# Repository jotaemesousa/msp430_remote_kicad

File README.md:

msp430_remote_kicad
===================

Kicad files for a remote using a msp430 MCU and a nrf24 transceiver from Nordic

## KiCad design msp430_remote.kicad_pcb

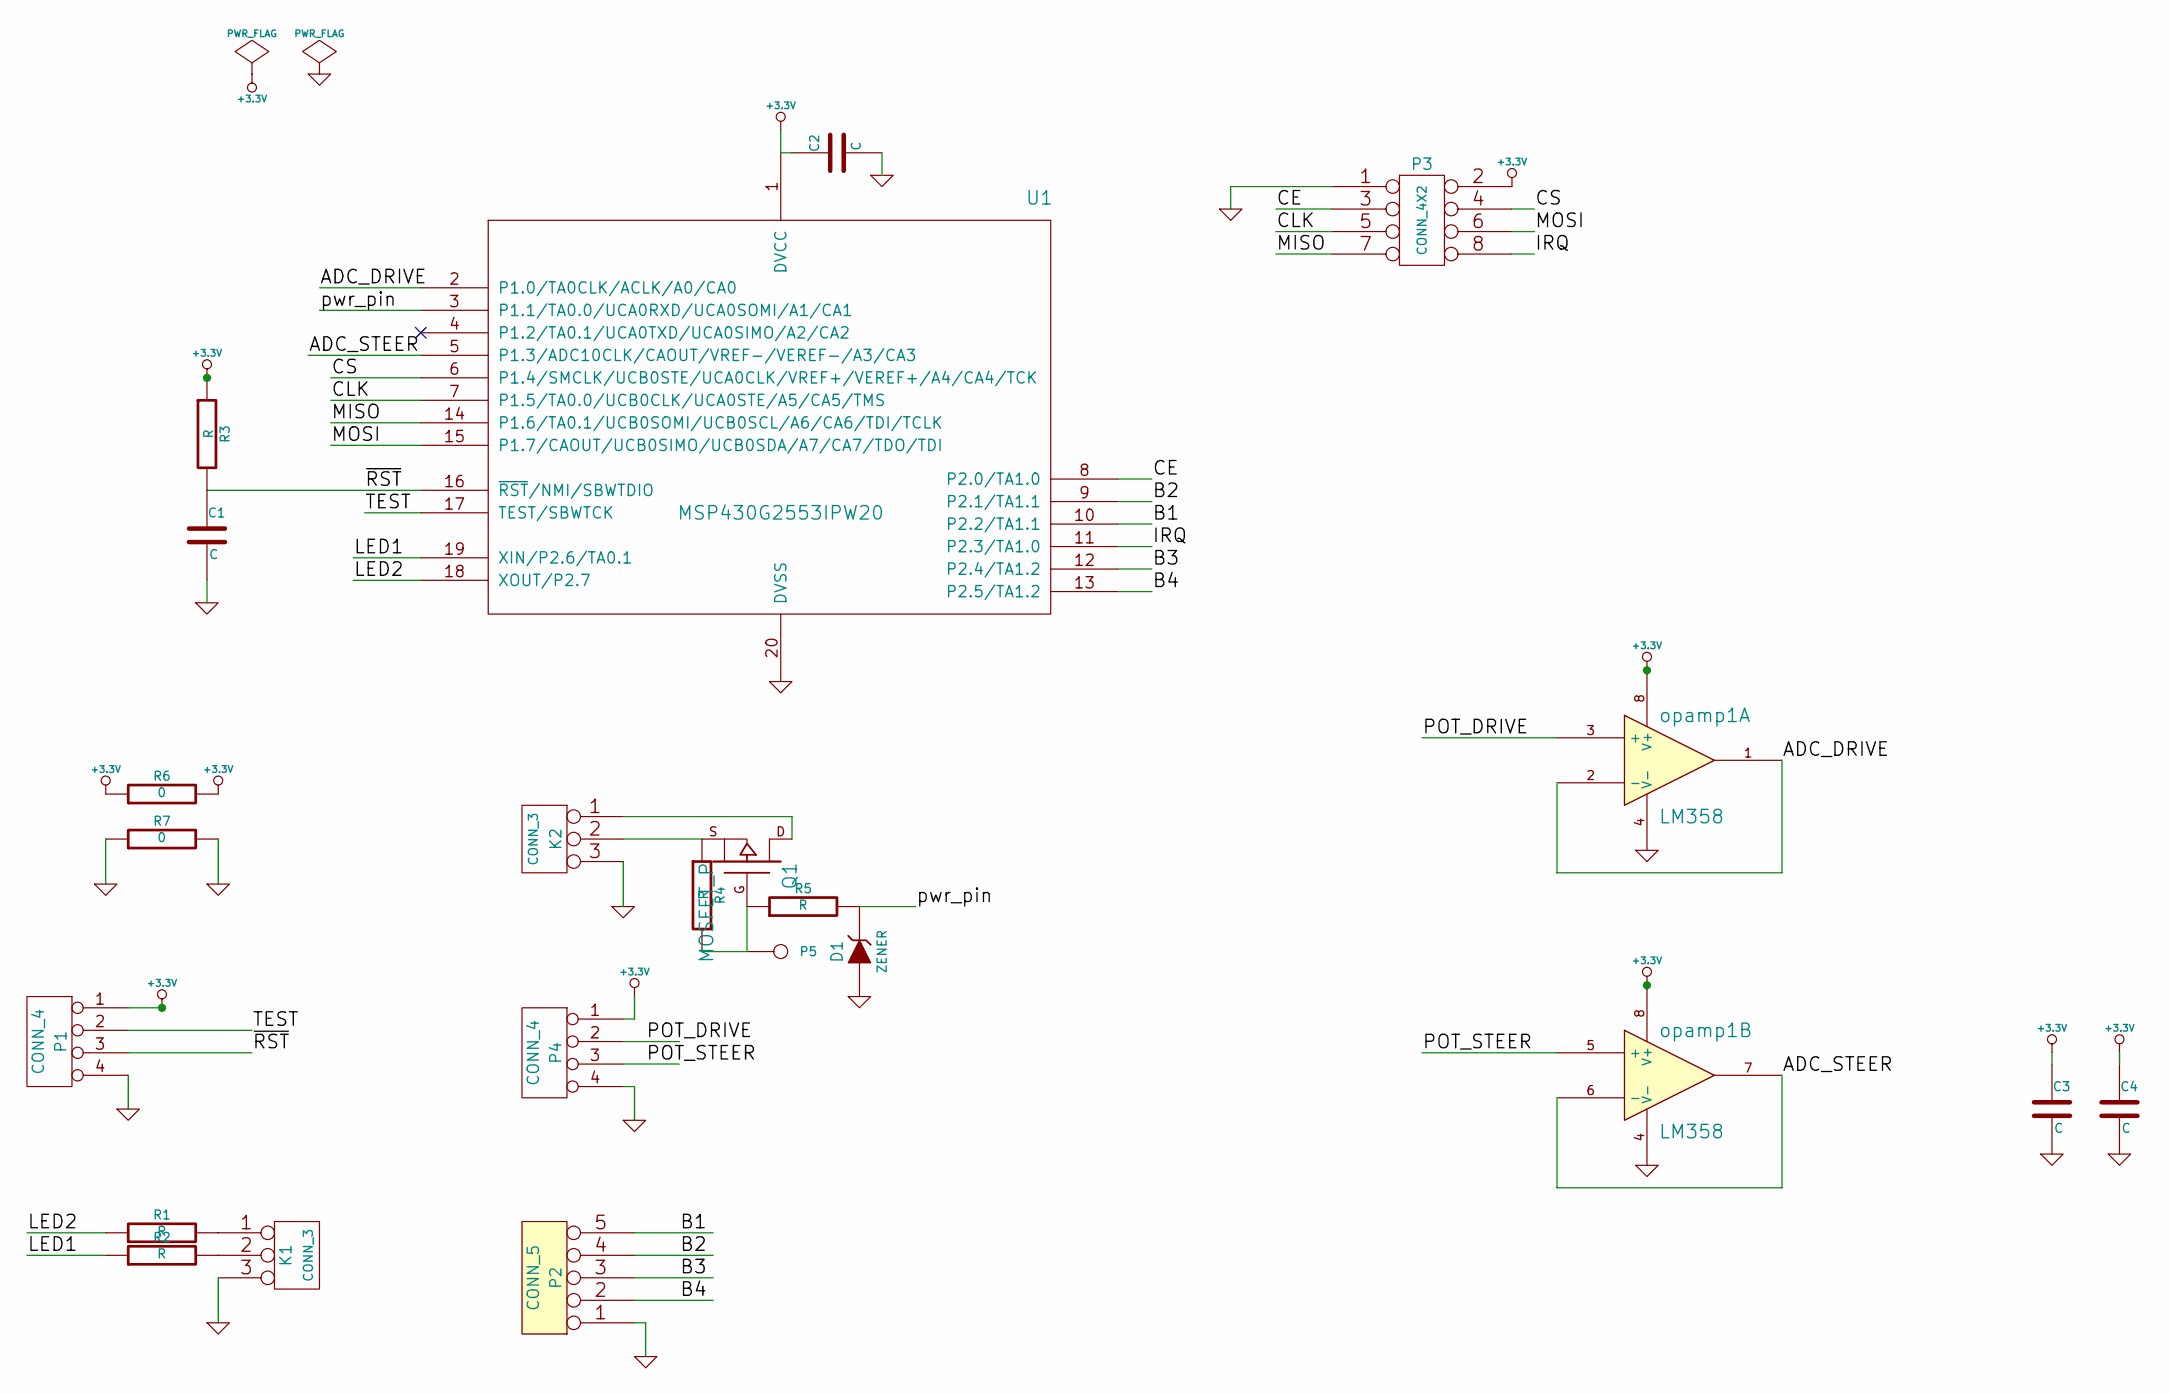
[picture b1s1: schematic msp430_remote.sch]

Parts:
C1, C2, C3, C4: C
D1: ZENER
K1, K2: CONN_3
P1, P4: CONN_4
P2: CONN_5
P3: CONN_4X2
P5: CONN_1
Q1: MOSFET_P
R1, R2, R3, R4, R5: R
R6, R7: 0
U1: MSP430G2553IPW20
opamp1: LM358

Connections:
+3.3V: C2.1, C3.1, C4.1, P1.1, P3.2, P4.1, R3.1, R6.1, R6.2, U1.1 (DVCC), opamp1.8 (V+)
/ADC_DRIVE: U1.2 (P1.0/TA0CLK/ACLK/A0/CA0), opamp1.1, opamp1.2 (-)
/ADC_STEER: U1.5 (P1.3/ADC10CLK/CAOUT/VREF-/VEREF-/A3/CA3), opamp1.6 (-), opamp1.7
/B1: P2.5, U1.10 (P2.2/TA1.1)
/B2: P2.4, U1.9 (P2.1/TA1.1)
/B3: P2.3, U1.12 (P2.4/TA1.2)
/B4: P2.2, U1.13 (P2.5/TA1.2)
/CE: P3.3, U1.8 (P2.0/TA1.0)
/CLK: P3.5, U1.7 (P1.5/TA0.0/UCB0CLK/UCA0STE/A5/CA5/TMS)
/CS: P3.4, U1.6 (P1.4/SMCLK/UCB0STE/UCA0CLK/VREF+/VEREF+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)
/IRQ: P3.8, U1.11 (P2.3/TA1.0)
/LED1: R2.1, U1.19 (XIN/P2.6/TA0.1)
/LED2: R1.1, U1.18 (XOUT/P2.7)
/MISO: P3.7, U1.14 (P1.6/TA0.1/UCB0SOMI/UCB0SCL/A6/CA6/TDI/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)
/MOSI: P3.6, U1.15 (P1.7/CAOUT/UCB0SIMO/UCB0SDA/A7/CA7/TDO/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)
/POT_DRIVE: P4.2, opamp1.3 (+)
/POT_STEER: P4.3, opamp1.5 (+)
/TEST: P1.2, U1.17 (TEST/SBWTCK)
/pwr_pin: D1.2 (K), R5.2, U1.3 (P1.1/TA0.0/UCA0RXD/UCA0SOMI/A1/CA1)
/~RST: C1.1, P1.3, R3.2, U1.16 (~RST~/NMI/SBWTDIO)
GND: C1.2, C2.2, C3.2, C4.2, D1.1 (A), K1.3, K2.3, P1.4, P2.1, P3.1, P4.4, R7.1, R7.2, U1.20 (DVSS), opamp1.4 (V-)
unnamed: K1.1, R1.2
unnamed: K1.2 (PM), R2.2
unnamed: K2.1, Q1.D
unnamed: K2.2 (PM), Q1.S, R4.1
unnamed: P5.1, Q1.G, R4.2, R5.1

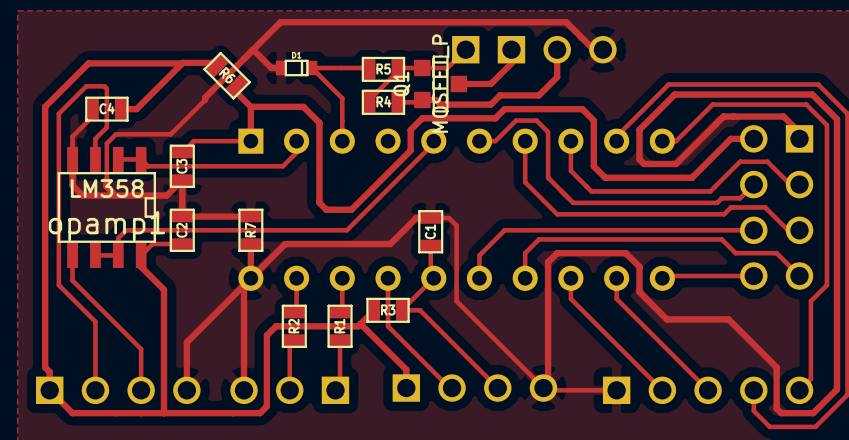
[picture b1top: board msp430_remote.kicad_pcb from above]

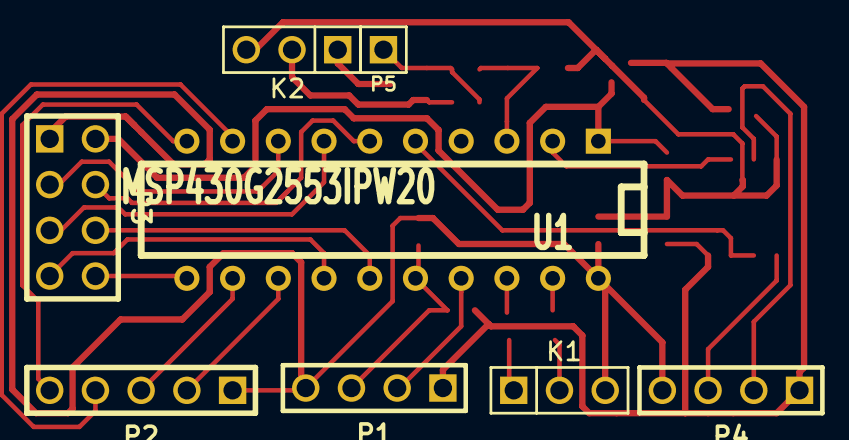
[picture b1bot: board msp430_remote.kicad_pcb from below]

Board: 2 copper layers, 22 parts (8 on the bottom side), 26 nets.

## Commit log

2013-05-23 falta o dc dc
2013-05-25 tudo_feito
2013-05-25 pistas mais largas e vias de .8
2013-05-25 done
2013-05-27 tentativa de por fet
2013-05-28 final
2013-05-31 zener alterad
